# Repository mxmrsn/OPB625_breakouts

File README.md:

# OPB625_breakouts
Breaks out OPB625 optical photointerruptor switch for non-contact-based limit switch applications.

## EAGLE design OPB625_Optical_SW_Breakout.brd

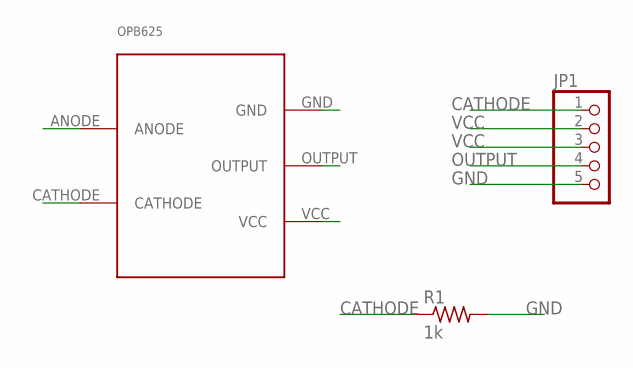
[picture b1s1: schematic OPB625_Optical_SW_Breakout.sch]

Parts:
JP1: PINHD-1X5; 1X05
R1: 1k; R0805
U$1: OPB625

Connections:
CATHODE: JP1.1, R1.1, U$1.CATHODE
GND: JP1.5, R1.2, U$1.GND
OUTPUT: JP1.4, U$1.OUTPUT
VCC: JP1.2, JP1.3, U$1.ANODE, U$1.VCC

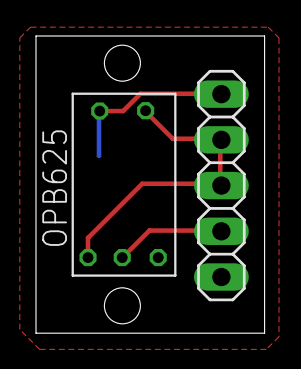
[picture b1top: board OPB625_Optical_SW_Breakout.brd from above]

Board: 2 copper layers, 12.7 x 16.5 mm, 3 parts (1 on the bottom side), 4 nets.
